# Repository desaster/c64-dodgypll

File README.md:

# 8701 replacement for C64.

This is a replacement 8701 chip for the Commodore 64 by using the ICS525-01
clock generator chip.

The chip configuration is based on the
[youtube comments by @iz8dwf](https://www.youtube.com/watch?v=ipQD7fEKG38)

This configuration is currently only for PAL C64's.

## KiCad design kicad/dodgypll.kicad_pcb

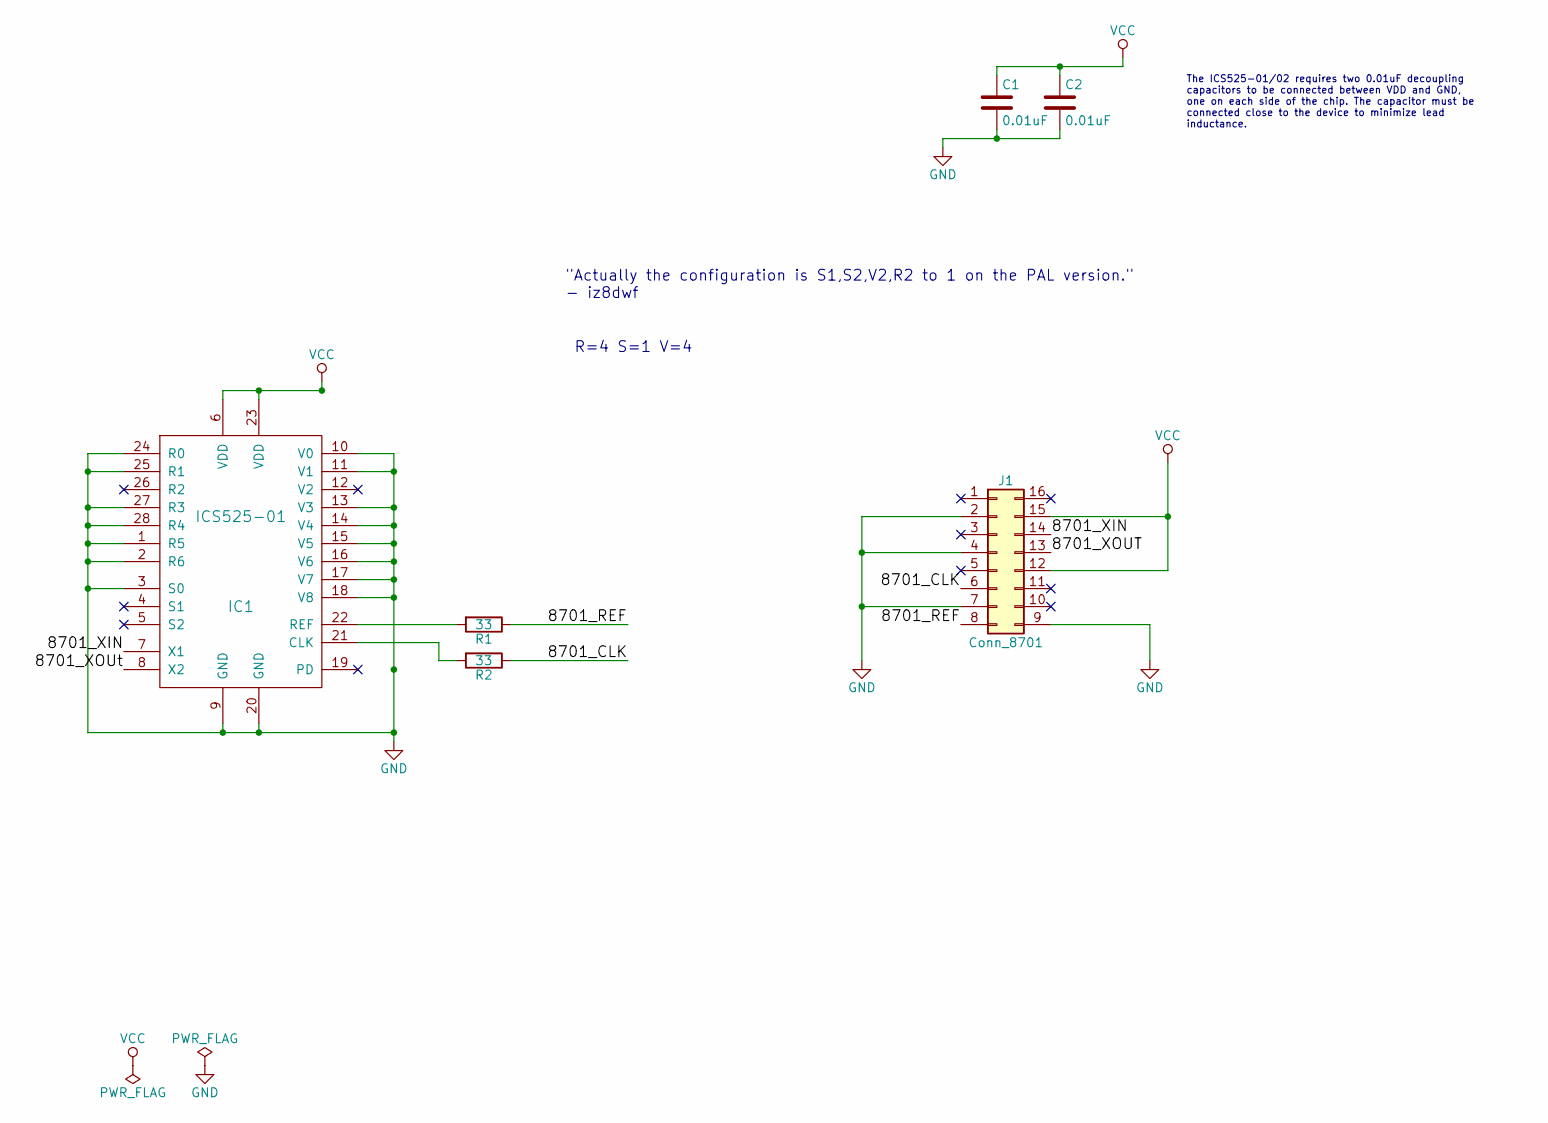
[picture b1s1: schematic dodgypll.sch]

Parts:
C1, C2: 0.01uF; C_0805
IC1: ICS525-01; SSOP-28_3.9x9.9mm_Pitch0.635mm_LongPads
J1: Conn_8701; DIP-16_W7.62mm_Socket_LongPads
R1, R2: 33; C_0805

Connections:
/8701_CLK: J1.6, R2.1
/8701_REF: J1.8, R1.1
/8701_XIN: IC1.7 (X1), J1.14
/8701_XOUT: IC1.8 (X2), J1.13
GND: C1.2, C2.2, IC1.1 (R5), IC1.2 (R6), IC1.3 (S0), IC1.9 (GND), IC1.10 (V0), IC1.11 (V1), IC1.13 (V3), IC1.14 (V4), IC1.15 (V5), IC1.16 (V6), IC1.17 (V7), IC1.18 (V8), IC1.20 (GND), IC1.24 (R0), IC1.25 (R1), IC1.27 (R3), IC1.28 (R4), J1.2, J1.4, J1.7, J1.9
unnamed: IC1.21 (CLK), R2.2
unnamed: IC1.22 (REF), R1.2
VCC: C1.1, C2.1, IC1.6 (VDD), IC1.23 (VDD), J1.12, J1.15

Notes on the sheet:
"Actually the configuration is S1,S2,V2,R2 to 1 on the PAL version." - iz8dwf
R=4 S=1 V=4
The ICS525-01/02 requires two 0.01uF decoupling capacitors to be connected between VDD and GND, one on each side of the chip. The capacitor must be connected close to the device to minimize lead inductance.

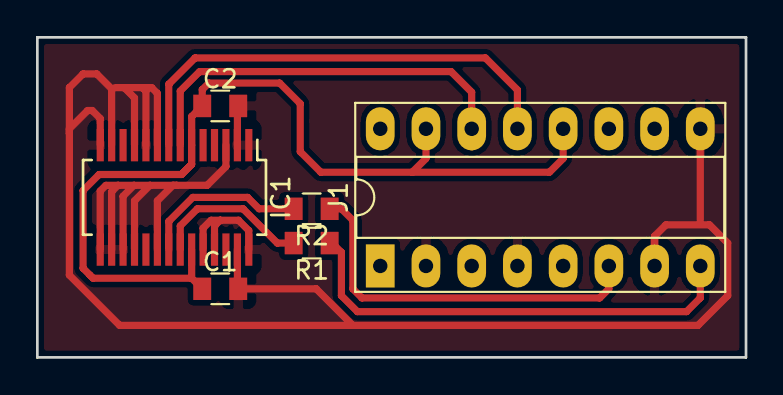
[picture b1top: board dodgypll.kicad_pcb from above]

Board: 2 copper layers, 39.4 x 17.8 mm, 6 parts (0 on the bottom side), 8 nets.

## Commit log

2018-01-29 Add kicad project
2018-01-29 Add README
2018-01-29 Add .gitignore
2018-01-29 Fix README
2018-01-29 Add schematic PDF
